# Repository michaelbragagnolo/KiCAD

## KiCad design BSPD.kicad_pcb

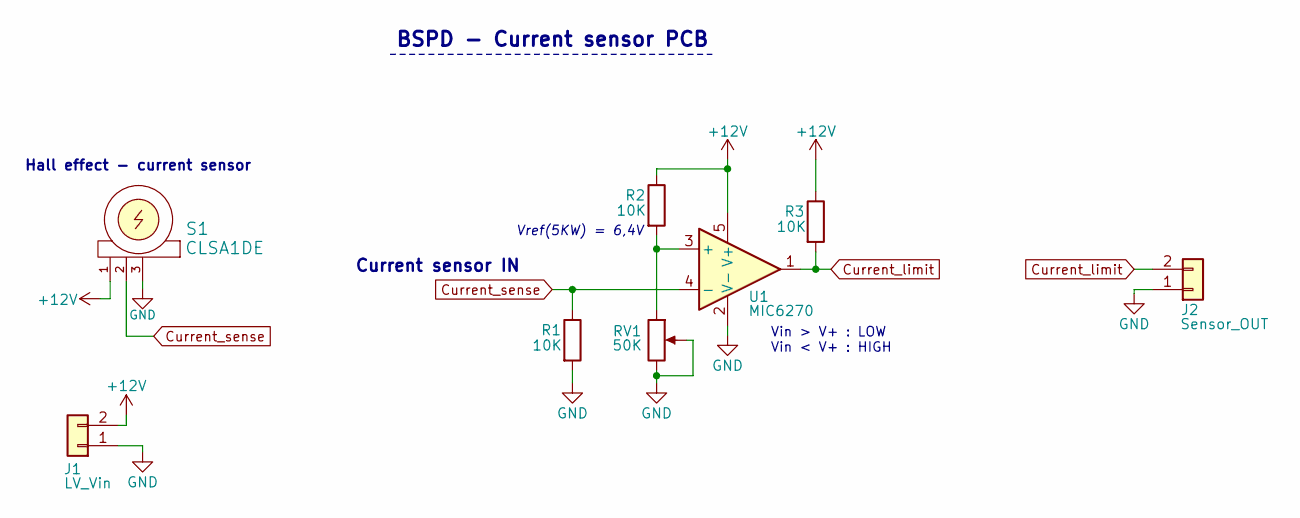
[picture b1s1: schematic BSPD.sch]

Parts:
J1: LV_Vin; SL-102-X-XX_1x02
J2: Sensor_OUT; SL-102-X-XX_1x02
R1, R2, R3: 10K; R_1210_HandSoldering
RV1: 50K; Potentiometer_Trimmer_Bourns_3296W
S1: CLSA1DE; SL-103-X-XX_1x03
U1: MIC6270; SOT-23-5_HandSoldering

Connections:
+12V: J1.2, R2.1, R3.1, S1.1, U1.5 (V+)
Current_limit: J2.2, R3.2, U1.1
Current_sense: R1.1, S1.2, U1.4 (-)
GND: J1.1, J2.1, R1.2, RV1.2, RV1.3, S1.3, U1.2 (V-)
unnamed: R2.2, RV1.1, U1.3 (+)

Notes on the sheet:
BSPD - Current sensor PCB
Vin > V+ : LOW Vin < V+ : HIGH
Current sensor IN
Vref(5KW) = 6,4V
Hall effect - current sensor

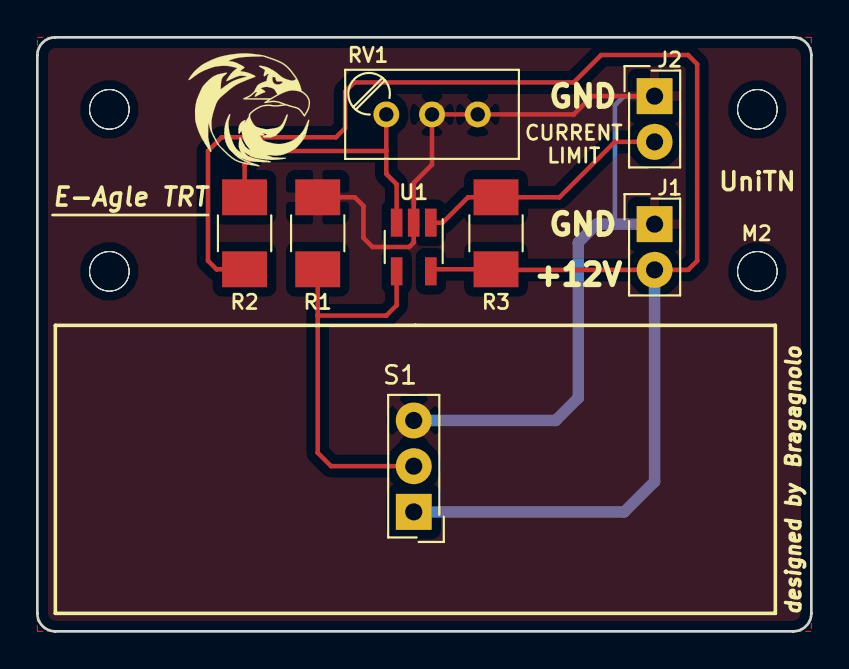
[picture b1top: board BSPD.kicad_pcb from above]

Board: 2 copper layers, 43.0 x 33.0 mm, 9 parts (0 on the bottom side), 5 nets.

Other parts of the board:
M2: MountingHole_2.2mm_M2
